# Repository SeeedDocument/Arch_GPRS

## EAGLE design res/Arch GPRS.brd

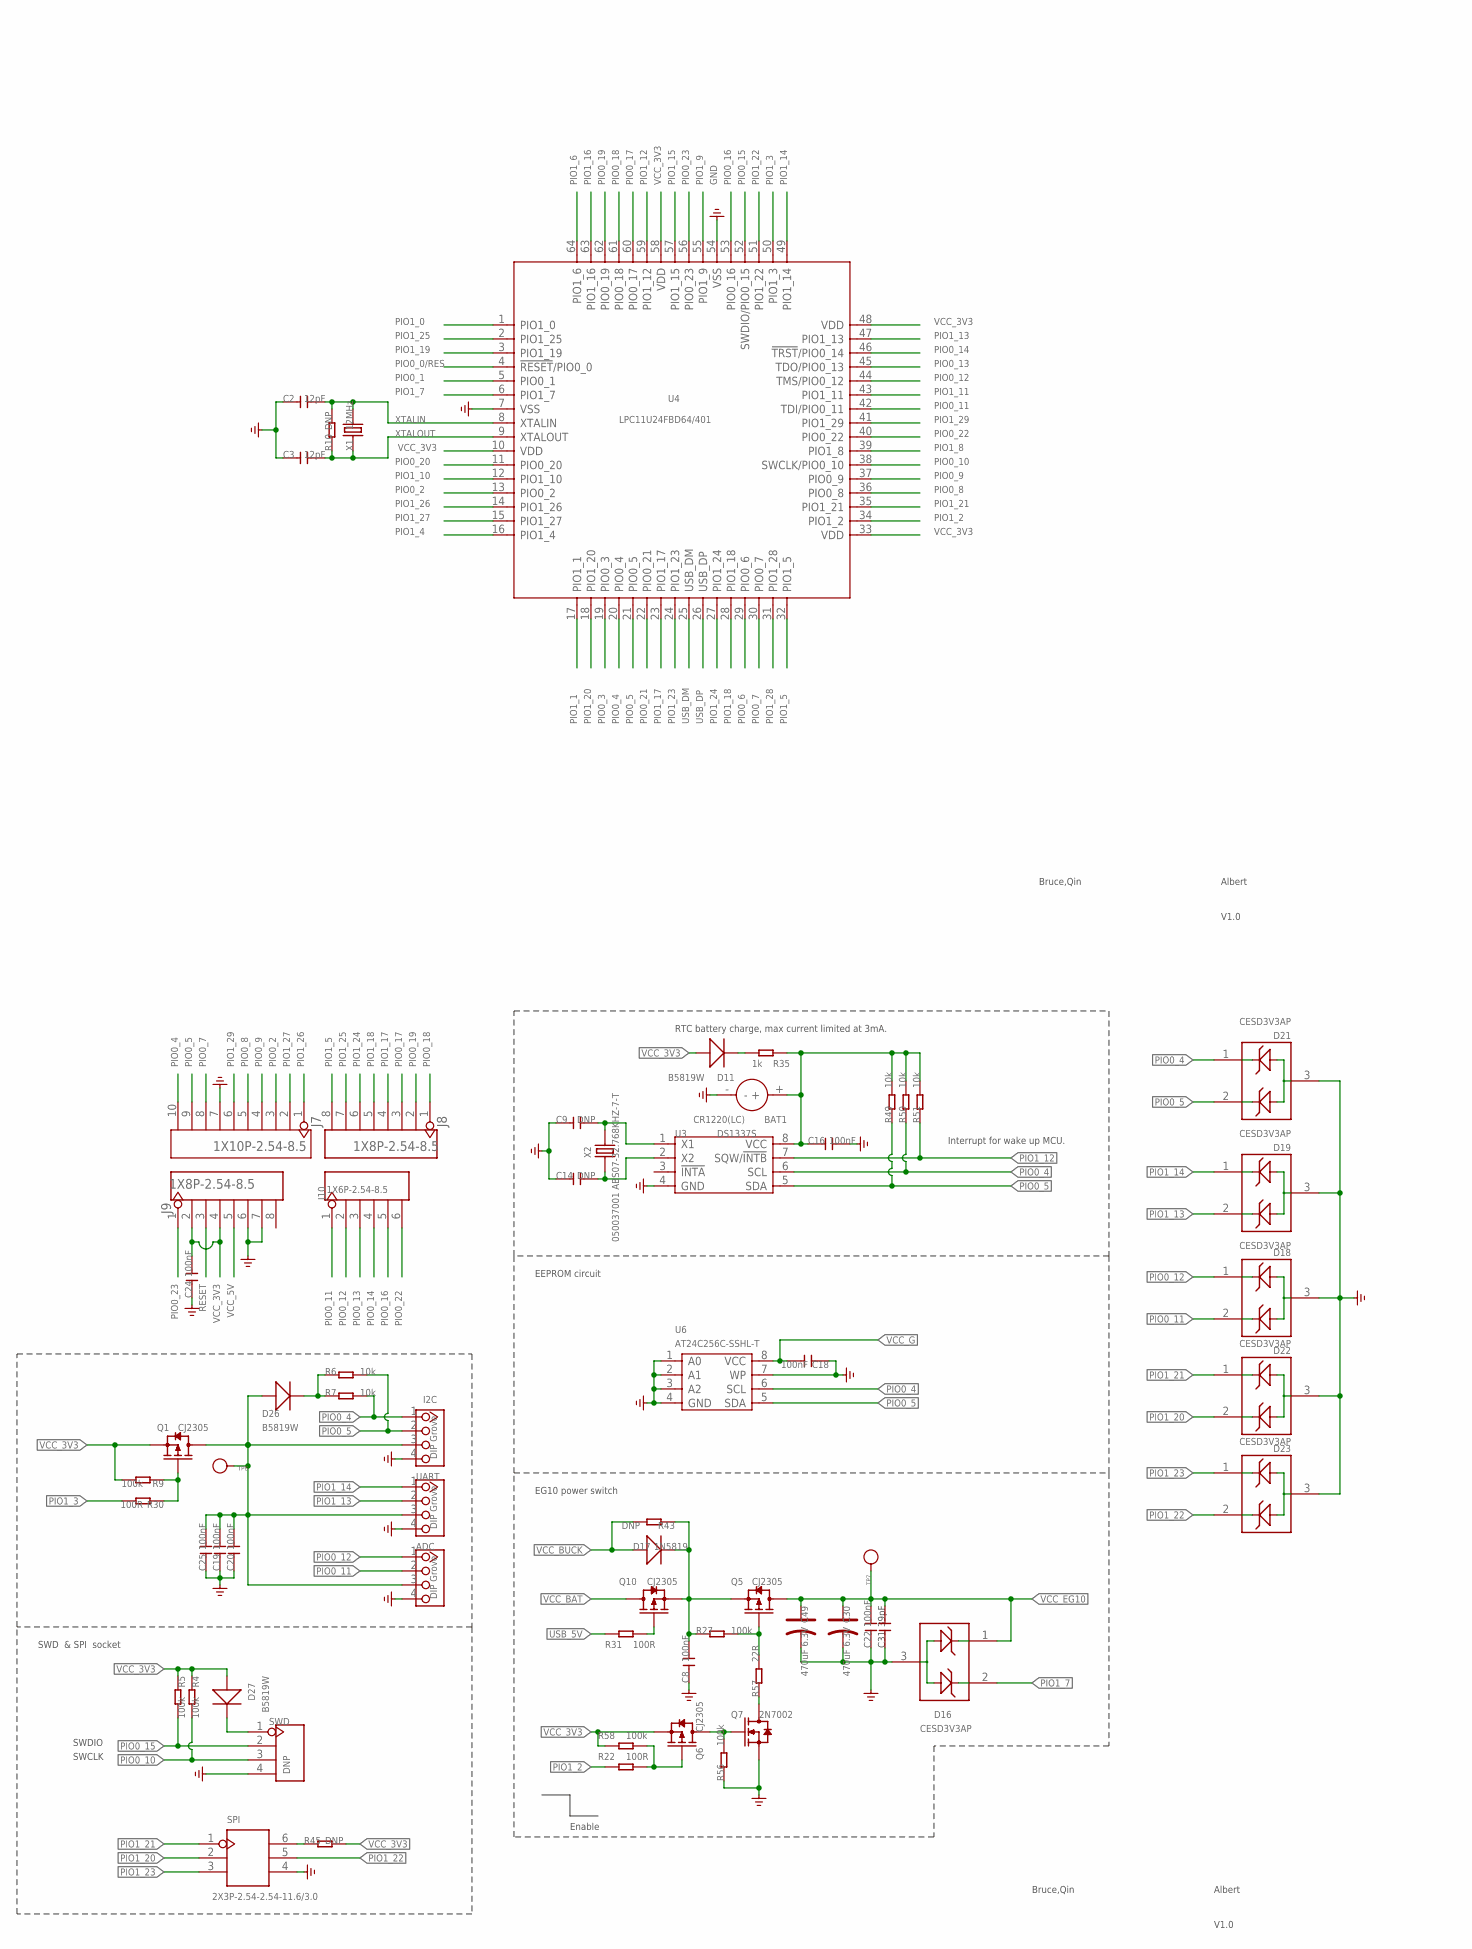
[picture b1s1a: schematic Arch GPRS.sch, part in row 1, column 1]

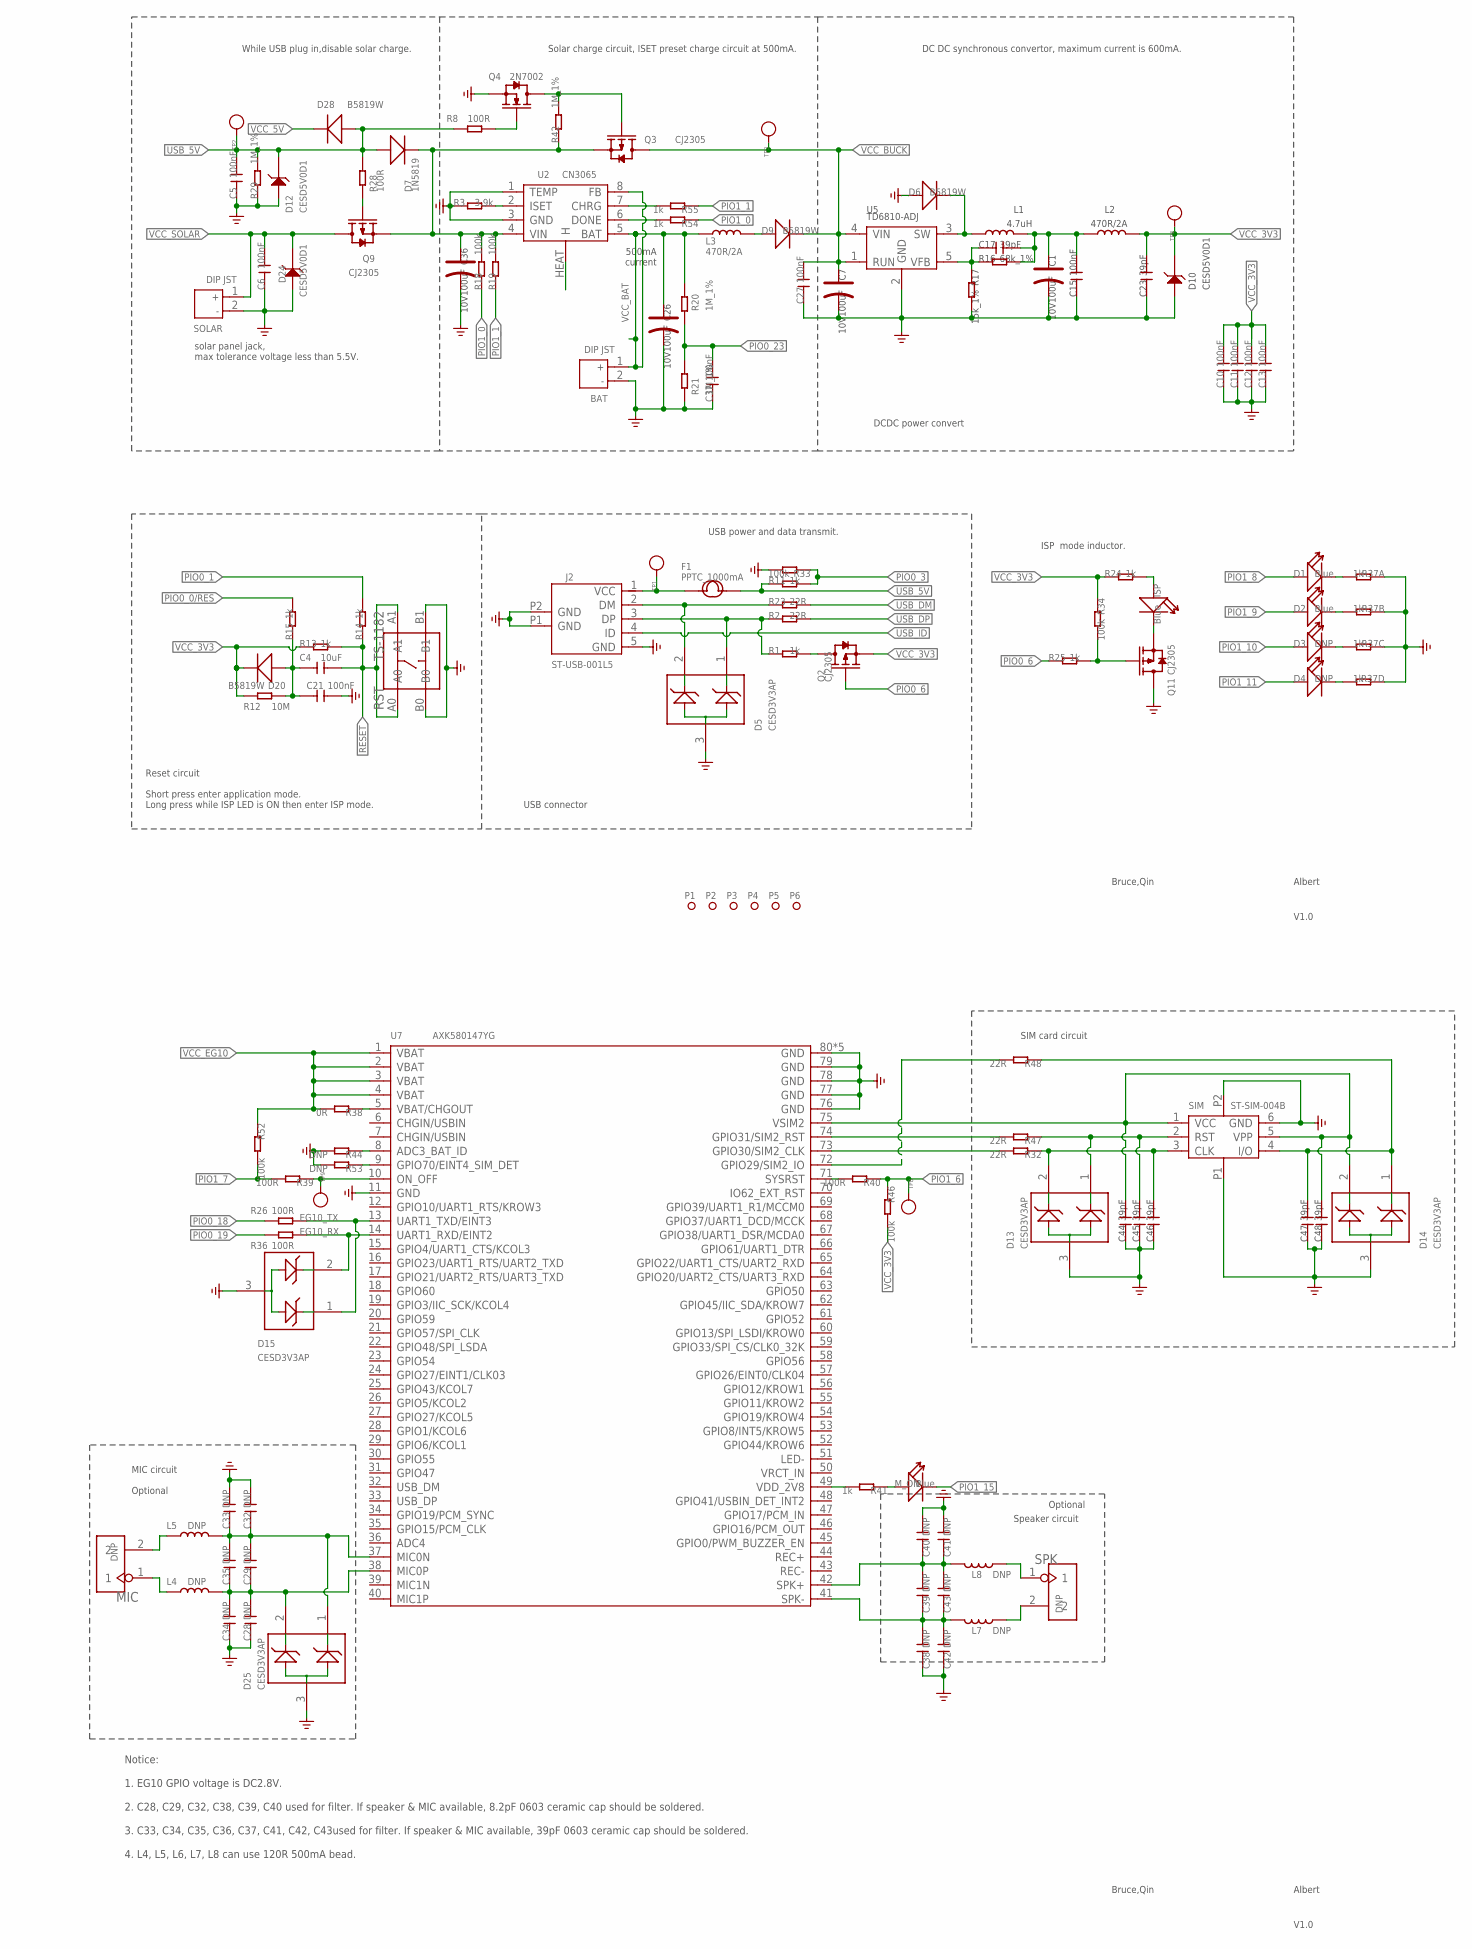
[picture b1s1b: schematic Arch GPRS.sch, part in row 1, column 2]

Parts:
ADC: DIP Grove; 4P-2.0
BAT: DIP JST; JST-2.0
BAT1: CR1220(LC); 2P-D12.55X2.22H
C1, C7, C26, C36: 10V100uF; AVX-B
C2, C3: 12pF; C0603
C4: 10uF; C0805
C5, C6, C8, C10, C11, C12, C13, C15, C16, C18, C19, C20, C21, C22, C24, C25, C27, C37: 100nF; C0603
C9, C14, C28, C29, C32, C33, C34, C35, C38, C39, C40, C41, C42, C43: DNP; C0603
C17, C23, C31, C44, C45, C46, C47, C48: 39pF; C0603
C30, C49: 470uF 6.3V; AVX-D
D1, D2: Blue; LED-0603
D3, D4: DNP; LED-0603
D5, D13, D14, D15, D16, D18, D19, D21, D22, D23, D25: CESD3V3AP; SOT23
D6, D9, D11, D20, D26, D27, D28: B5819W; SOD123
D7, D17: 1N5819; SMA
D10, D12, D24: CESD5V0D1; SOD123-2.7X1.6
F1: PPTC_1000mA; F1206
I2C: DIP Grove; 4P-2.0
ISP: Blue; LED-0603
J2: ST-USB-001L5; MICRO-5P-180D
J7: 1X10P-2.54-8.5; 10P-2.54
J8, J9: 1X8P-2.54-8.5; 8P-2.54
J10: 1X6P-2.54-8.5; 6P-2.54-65/35MIL
L1: 4.7uH; L0420
L2, L3: 470R/2A; L0805
L4, L5, L7, L8: DNP; L0603
MIC: DNP; 2P-2.0
M_ON: Blue; LED-0603
P1, P2, P3, P4, P5, P6: PAD-MARK; ROUND-MARK-1.0
Q1, Q2, Q3, Q5, Q6, Q9, Q10, Q11: CJ2305; SOT23
Q4, Q7: 2N7002; SOT23
R1, R11, R13, R14, R15, R24, R25, R35, R41, R54, R55: 1k; R0603
R2, R23, R32, R47, R48, R57: 22R; R0603
R3: 3.9k; R0603
R4, R5, R9, R18, R19, R27, R33, R34, R46, R52, R56, R58: 100k; R0603
R6, R7, R49, R50, R51: 10k; R0603
R8, R22, R26, R28, R30, R31, R36, R39, R40: 100R; R0603
R10, R43, R44, R45, R53: DNP; R0603
R12: 10M; R0603
R16: 68k_1%; R0603
R17: 15k_1%; R0603
R20, R21, R29, R42: 1M_1%; R0603
R37: 1k; 1206-8-3.3X2.4
R38: 0R; R0603
RST: TS-1182; 4P-SMD-3.4X3.4X1.3H
SIM: ST-SIM-004B; 6P-1.8
SOLAR: DIP JST; JST-2.0
SPI: 2X3P-2.54-2.54-11.6/3.0; 2X3P-2.54
SPK: DNP; 2P-2.0
SWD: DNP; 4P-65/35MIL
TP1, TP2, TP3, TP4, TP6, TP7, TP8, TP9: PAD-TEST-POINT'4545'; TP_4545
U2: CN3065; DFN8
U3: DS1337S; SOP8
U4: LPC11U24FBD64/401; LQFP64
U5: TD6810-ADJ; SOT23-5
U6: AT24C256C-SSHL-T; SOIC8-6.0
U7: AXK580147YG; 80P-0.5-3H
UART: DIP Grove; 4P-2.0
X1: 12MHz; 2P-SMD-5X3.2
X2: 050037001 ABS07-32.768KHZ-7-T; 2P-SMD-3.2X1.5

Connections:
EG10_2V8: R41.2, U7.49 (VDD_2V8)
EG10_MIC0+: C28.2, C29.1, C34.2, C35.1, D25.2, L4.2, U7.38 (MIC0P)
EG10_MIC0+1: C39.2, C40.1, C41.1, C43.2, L8.1, U7.42 (SPK+)
EG10_MIC0-: C29.2, C32.1, C33.1, C35.2, D25.1, L5.2, U7.37 (MIC0N)
EG10_RST: R40.2, U7.71 (SYSRST)
EG10_RX: D15.2, R36.1, U7.14 (UART1_RXD/EINT2)
EG10_SIM_CLK: C46.2, D13.2, R32.1, SIM.3 (CLK)
EG10_SIM_IO: C47.2, D14.1, R48.1, SIM.4 (I/O)
EG10_SIM_RST: C45.2, D13.1, R47.1, SIM.2 (RST)
EG10_SIM_VCC: C44.2, C48.2, D14.2, SIM.1 (VCC), SIM.5 (VPP), U7.75 (VSIM2)
EG10_SPK-: C38.2, C39.1, C42.2, C43.1, L7.1, U7.41 (SPK-)
EG10_TX: D15.1, R26.1, U7.13 (UART1_TXD/EINT3)
GND: ADC.4, BAT.2, BAT1.-, C1.-, C2.1, C3.1, C5.1, C6.1, C7.-, C8.1, C9.1, C10.1, C11.1, C12.1, C13.1, C14.1, C15.1, C16.2, C18.1, C19.1, C20.1, C21.1, C22.1, C23.1, C24.1, C25.1, C26.-, C27.1, C28.1, C30.-, C31.1, C32.2, C33.2, C34.1, C36.-, C37.1, C38.1, C40.2, C41.2, C42.1, C44.1, C45.1, C46.1, C47.1, C48.1, C49.-, D5.3, D6.+, D10.1, D12.1, D13.3, D14.3, D15.3, D16.3, D18.3, D19.3, D21.3, D22.3, D23.3, D24.1, D25.3, I2C.4, J2.5 (GND), J2.P1 (GND), J2.P2 (GND), J7.7, J9.6, J9.7, Q4.2 (S), Q7.2 (S), Q11.3 (D), R3.1, R17.2, R21.1, R29.1, R33.2, R37.1, R37.2 (1), R37.3 (1), R37.4 (1), R44.2, R53.2, R56.1, RST.B0, RST.B1, SIM.6 (GND), SIM.P1 (7), SIM.P2 (8), SOLAR.2, SPI.4, SWD.4, U2.1 (TEMP), U2.3 (GND), U3.4 (GND), U4.7 (VSS), U4.54 (VSS), U5.2 (GND), U6.1 (A0), U6.2 (A1), U6.3 (A2), U6.4 (GND), U6.7 (WP), U7.11 (GND), U7.76 (GND), U7.77 (GND), U7.78 (GND), U7.79 (GND), U7.80 (GND), U7.P1 (GND), U7.P2 (GND), U7.P3 (GND), U7.P4 (GND), UART.4
HEAT: U2.HEAT (H)
unnamed: D27.-, SWD.1
unnamed: D4.-, R37.5 (2)
unnamed: Q2.3 (D), R1.2
unnamed: Q5.1 (G), R27.2, R57.2
unnamed: R3.2, U2.2 (ISET)
unnamed: D11.-, R35.1
unnamed: C4.2, C21.2, D20.+, R12.2, R15.1
unnamed: Q3.1 (G), Q4.3 (D), R42.2
unnamed: C8.2, D17.1 (-), Q5.2 (S), Q10.2 (S), R27.1, R43.1
unnamed: D9.+, L3.2
unnamed: R48.2, U7.72 (GPIO29/SIM2_IO)
unnamed: Q1.1 (G), R9.1, R30.1
unnamed: C14.2, U3.2 (X2), X2.1
unnamed: C9.2, U3.1 (X1), X2.2
unnamed: Q11.1 (G), R25.2, R34.2
unnamed: ISP.-, Q11.2 (S)
unnamed: D3.-, R37.6 (2)
unnamed: ISP.+, R24.2
unnamed: D2.-, R37.7 (2)
unnamed: R47.2, U7.74 (GPIO31/SIM2_RST)
unnamed: R38.1, U7.5 (VBAT/CHGOUT)
unnamed: M_ON.+, R41.1
unnamed: R45.1, SPI.6
unnamed: BAT1.+, C16.1, R35.2, R49.2, R50.2, R51.2, U3.8 (VCC)
unnamed: R32.2, U7.73 (GPIO30/SIM2_CLK)
unnamed: R39.1, TP9.T, U7.10 (ON_OFF)
unnamed: Q10.1 (G), R31.1
unnamed: L5.1, MIC.2
unnamed: D6.-, L1.1, U5.3 (SW)
unnamed: D1.-, R37.8 (2)
unnamed: L4.1, MIC.1
unnamed: L7.2, SPK.2
unnamed: Q9.1 (G), R28.1
unnamed: L8.2, SPK.1
unnamed: D5.2, J2.2 (DM), R23.1
unnamed: D5.1, J2.3 (DP), R1.1, R2.1
unnamed: C36.+, D7.1 (-), Q3.2 (S), Q9.2 (S), R18.2, R19.2, R42.1, U2.4 (VIN)
unnamed: F1.1, J2.1 (VCC), TP1.T
unnamed: C17.1, R16.1, R17.1, U5.5 (VFB)
unnamed: Q4.1 (G), R8.1
unnamed: R44.1, U7.8 (ADC3_BAT_ID)
unnamed: R53.1, U7.9 (GPIO70/EINT4_SIM_DET)
unnamed: R55.2, U2.7 (CHRG)
unnamed: R54.2, U2.6 (DONE)
unnamed: Q7.3 (D), R57.1
unnamed: Q6.3 (D), Q7.1 (G), R56.2
unnamed: C1.+, C15.2, C17.2, L1.2, L2.1, R16.2
unnamed: Q6.1 (G), R22.1, R58.1
PIO0_0/RES: R15.2, U4.4 (!RESET!/PIO0_0)
PIO0_1: R14.2, U4.5 (PIO0_1)
PIO0_2: J7.3, U4.13 (PIO0_2)
PIO0_3: R11.2, R33.1, U4.19 (PIO0_3)
PIO0_4: D21.1, I2C.1, J7.10, R7.2, R50.1, U3.6 (SCL), U4.20 (PIO0_4), U6.6 (SCL)
PIO0_5: D21.2, I2C.2, J7.9, R6.2, R49.1, U3.5 (SDA), U4.21 (PIO0_5), U6.5 (SDA)
PIO0_6: Q2.1 (G), R25.1, U4.29 (PIO0_6)
PIO0_7: J7.8, U4.30 (PIO0_7)
PIO0_8: J7.5, U4.36 (PIO0_8)
PIO0_9: J7.4, U4.37 (PIO0_9)
PIO0_10: R4.2, SWD.3, U4.38 (SWCLK/PIO0_10)
PIO0_11: ADC.2, D18.2, J10.1, U4.42 (TDI/PIO0_11)
PIO0_12: ADC.1, D18.1, J10.2, U4.44 (TMS/PIO0_12)
PIO0_13: J10.3, U4.45 (TDO/PIO0_13)
PIO0_14: J10.4, U4.46 (!TRST!/PIO0_14)
PIO0_15: R5.2, SWD.2, U4.52 (SWDIO/PIO0_15)
PIO0_16: J10.5, U4.53 (PIO0_16)
PIO0_17: J8.3, U4.60 (PIO0_17)
PIO0_18: J8.1, R26.2, U4.61 (PIO0_18)
PIO0_19: J8.2, R36.2, U4.62 (PIO0_19)
PIO0_20: U4.11 (PIO0_20)
PIO0_21: U4.22 (PIO0_21)
PIO0_22: J10.6, U4.40 (PIO0_22)
PIO0_23: C37.2, J9.1, R20.1, R21.2, U4.56 (PIO0_23)
PIO1_0: R18.1, R54.1, U4.1 (PIO1_0)
PIO1_1: R19.1, R55.1, U4.17 (PIO1_1)
PIO1_2: R22.2, U4.34 (PIO1_2)
PIO1_3: R30.2, U4.50 (PIO1_3)
PIO1_4: U4.16 (PIO1_4)
PIO1_5: J8.8, U4.32 (PIO1_5)
PIO1_6: R40.1, R46.1, TP8.T, U4.64 (PIO1_6)
PIO1_7: D16.2, R39.2, R52.2, U4.6 (PIO1_7)
PIO1_8: D1.+, U4.39 (PIO1_8)
PIO1_9: D2.+, U4.55 (PIO1_9)
PIO1_10: D3.+, U4.12 (PIO1_10)
PIO1_11: D4.+, U4.43 (PIO1_11)
PIO1_12: R51.1, U3.7 (SQW/!INTB), U4.59 (PIO1_12)
PIO1_13: D19.2, U4.47 (PIO1_13), UART.2
PIO1_14: D19.1, U4.49 (PIO1_14), UART.1
PIO1_15: M_ON.-, U4.57 (PIO1_15)
PIO1_16: U4.63 (PIO1_16)
PIO1_17: J8.4, U4.23 (PIO1_17)
PIO1_18: J8.5, U4.28 (PIO1_18)
PIO1_19: U4.3 (PIO1_19)
PIO1_20: D22.2, SPI.2, U4.18 (PIO1_20)
PIO1_21: D22.1, SPI.1, U4.35 (PIO1_21)
PIO1_22: D23.2, SPI.5, U4.51 (PIO1_22)
PIO1_23: D23.1, SPI.3, U4.24 (PIO1_23)
PIO1_24: J8.6, U4.27 (PIO1_24)
PIO1_25: J8.7, U4.2 (PIO1_25)
PIO1_26: J7.1, U4.14 (PIO1_26)
PIO1_27: J7.2, U4.15 (PIO1_27)
PIO1_28: U4.31 (PIO1_28)
PIO1_29: J7.6, U4.41 (PIO1_29)
RESET: C4.1, J9.3, R13.2, R14.1, RST.A0, RST.A1
USB_5V: C5.2, D7.2 (+), D12.2, D28.+, F1.2, R8.2, R11.1, R28.2, R29.2, R31.2, TP2.T
USB_DM: R23.2, U4.25 (USB_DM)
USB_DP: R2.2, U4.26 (USB_DP)
USB_ID: J2.4 (ID)
VCC_3V3: C10.2, C11.2, C12.2, C13.2, C23.2, C24.2, D10.2, D11.+, D20.-, D27.+, J9.2, J9.4, L2.2, Q1.2 (S), Q2.2 (S), Q6.2 (S), R4.1, R5.1, R9.2, R12.1, R13.1, R24.1, R34.1, R45.2, R46.2, R58.2, TP4.T, U4.10 (VDD), U4.33 (VDD), U4.48 (VDD), U4.58 (VDD)
VCC_5V: D28.-, J9.5
VCC_BAT: BAT.1, C26.+, L3.1, Q10.3 (D), R20.2, U2.5 (BAT), U2.8 (FB)
VCC_BUCK: C7.+, C27.2, D9.-, D17.2 (+), Q3.3 (D), R43.2, TP3.T, U5.1 (RUN), U5.4 (VIN)
VCC_EG10: C22.2, C30.+, C31.2, C49.+, D16.1, Q5.3 (D), R38.2, R52.1, TP7.T, U7.1 (VBAT), U7.2 (VBAT), U7.3 (VBAT), U7.4 (VBAT)
VCC_G: ADC.3, C18.2, C19.2, C20.2, C25.2, D26.+, I2C.3, Q1.3 (D), TP6.T, U6.8 (VCC), UART.3
VCC_I2C: D26.-, R6.1, R7.1
VCC_SOLAR: C6.2, D24.2, Q9.3 (D), SOLAR.1
XTALIN: C2.2, R10.2, U4.8 (XTALIN), X1.2
XTALOUT: C3.2, R10.1, U4.9 (XTALOUT), X1.1

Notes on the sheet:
Bruce,Qin
Albert
V1.0
SWDIO
SWCLK
DCDC power convert
Interrupt for wake up MCU.
500mA current
While USB plug in,disable solar charge.
Solar charge circuit, ISET preset charge circuit at 500mA.
DC DC synchronous convertor, maximum current is 600mA.
solar panel jack, max tolerance voltage less than 5.5V.
USB power and data transmit.
ISP mode inductor.
Notice: 1. EG10 GPIO voltage is DC2.8V. 2. C28, C29, C32, C38, C39, C40 used for filter. If speaker & MIC available, 8.2pF 0603 ceramic cap should be soldered. 3. C33, C34, C35, C36, C37, C41, C42, C43used for filter. If speaker & MIC available, 39pF 0603 ceramic cap should be soldered. 4. L4, L5, 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
RTC battery charge, max current limited at 3mA.
Optional
MIC circuit
Speaker circuit
SIM card circuit
SWD & SPI socket
EG10 power switch
Enable
Reset circuit Short press enter application mode. Long press while ISP LED is ON then enter ISP mode.
USB connector
EEPROM circuit

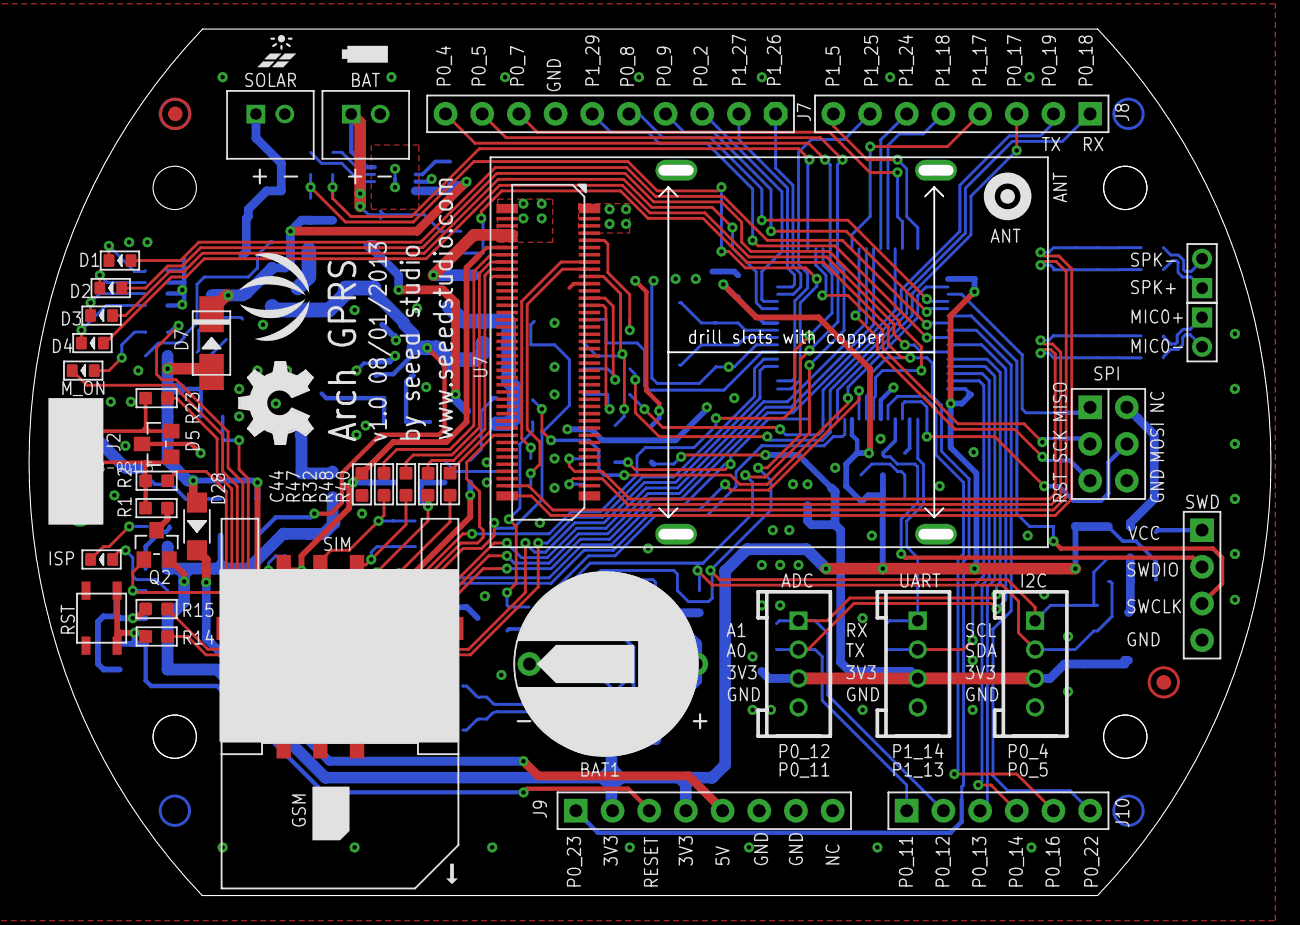
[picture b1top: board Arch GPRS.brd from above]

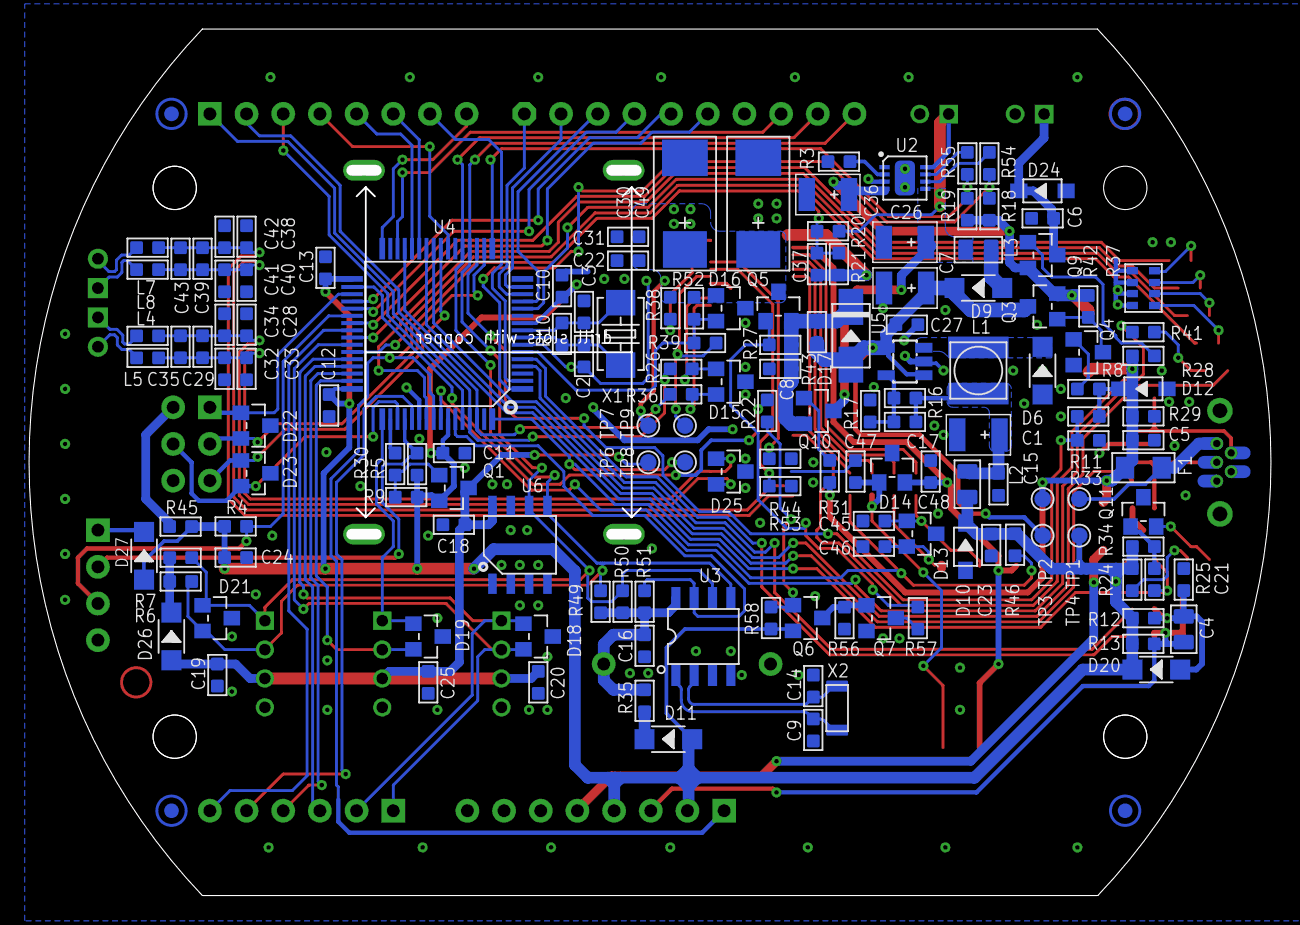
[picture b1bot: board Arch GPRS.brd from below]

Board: 2 copper layers, 86.0 x 60.0 mm, 195 parts (153 on the bottom side), 123 nets.

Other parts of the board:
U$55: LOGO_SILK
U$56: OSHW_FILLX200_NOTEXT

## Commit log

2017-06-01 upgrade
